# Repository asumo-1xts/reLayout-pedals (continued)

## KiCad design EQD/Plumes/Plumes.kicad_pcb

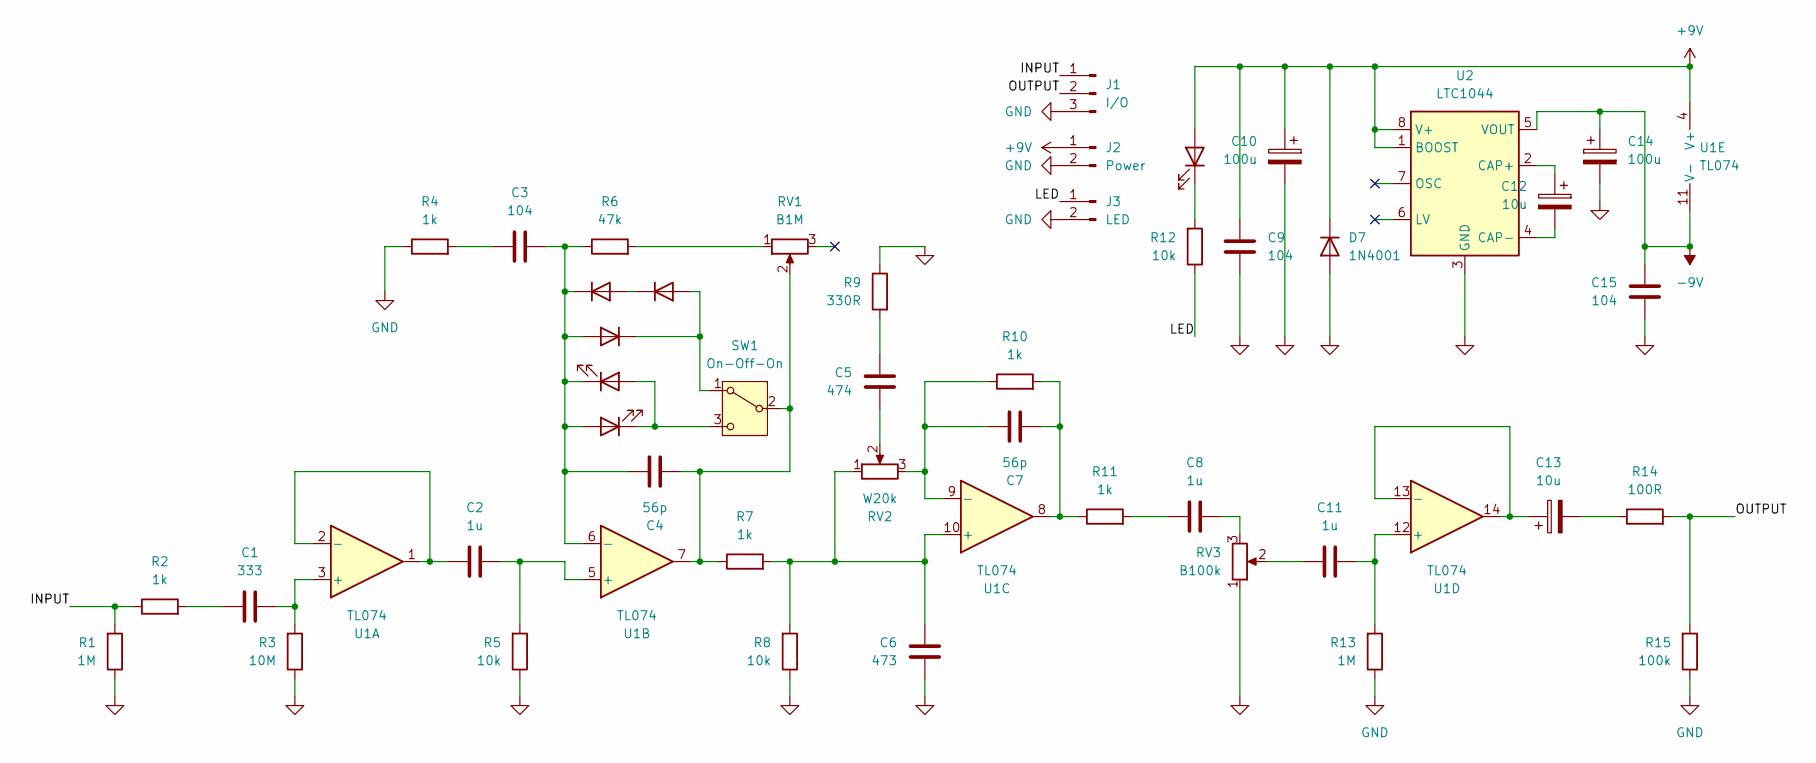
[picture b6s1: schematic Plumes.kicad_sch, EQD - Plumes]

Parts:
C1: 333; C_Rect_L7.2mm_W4.5mm_P5.00mm_FKS2_FKP2_MKS2_MKP2
C2, C8, C11: 1u; C_Rect_L7.0mm_W6.5mm_P5.00mm
C3: 104; C_Rect_L10.3mm_W5.7mm_P7.50mm_MKS4
C4, C7: 56p; C_Disc_D3.8mm_W2.6mm_P2.50mm
C5: 474; C_Rect_L7.2mm_W5.5mm_P5.00mm_FKS2_FKP2_MKS2_MKP2
C6: 473; C_Rect_L7.2mm_W4.5mm_P5.00mm_FKS2_FKP2_MKS2_MKP2
C9, C15: 104; C_Disc_D3.8mm_W2.6mm_P2.50mm
C10, C14: 100u; CP_Radial_D8.0mm_P3.50mm
C12, C13: 10u; CP_Radial_D5.0mm_P2.00mm
D1, D2, D5: 1N4148; D_DO-35_SOD27_P5.08mm_Vertical_AnodeUp
D3, D4, D6: LED; LED_D5.0mm
D7: 1N4001; D_DO-41_SOD81_P7.62mm_Horizontal
J1: I/O; PinHeader_1x03_P2.54mm_Vertical
J2: Power; PinHeader_1x02_P2.54mm_Vertical
J3: LED; PinHeader_1x02_P2.54mm_Vertical
R1, R13: 1M; R_Axial_DIN0207_L6.3mm_D2.5mm_P7.62mm_Horizontal
R2, R4, R7, R10, R11: 1k; R_Axial_DIN0207_L6.3mm_D2.5mm_P7.62mm_Horizontal
R3: 10M; R_Axial_DIN0207_L6.3mm_D2.5mm_P7.62mm_Horizontal
R5, R8, R12: 10k; R_Axial_DIN0207_L6.3mm_D2.5mm_P7.62mm_Horizontal
R6: 47k; R_Axial_DIN0207_L6.3mm_D2.5mm_P7.62mm_Horizontal
R9: 330R; R_Axial_DIN0207_L6.3mm_D2.5mm_P7.62mm_Horizontal
R14: 100R; R_Axial_DIN0207_L6.3mm_D2.5mm_P7.62mm_Horizontal
R15: 100k; R_Axial_DIN0207_L6.3mm_D2.5mm_P7.62mm_Horizontal
RV1: B1M; Potentiometer_Omeg_PC16BU_Vertical
RV2: W20k; Potentiometer_Omeg_PC16BU_Vertical
RV3: B100k; Potentiometer_Omeg_PC16BU_Vertical
SW1: On-Off-On; PinHeader_1x03_P2.54mm_Vertical
U1: TL074; DIP-14_W7.62mm
U2: LTC1044; DIP-8_W7.62mm

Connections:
+9V: C9.2, C10.1, D6.2 (A), D7.1 (K), J2.1, U1.4 (V+), U2.1 (BOOST), U2.8 (V+)
-9V: C14.1, C15.2, U1.11 (V-), U2.5 (VOUT)
/INPUT: J1.1, R1.2, R2.1
/LED: J3.1, R12.1
/OUTPUT: J1.2, R14.2, R15.2
GND: C6.1, C9.1, C10.2, C14.2, C15.1, D7.2 (A), J1.3, J2.2, J3.2, R1.1, R3.1, R4.1, R5.1, R8.1, R9.1, R13.1, R15.1, RV3.1, U2.3 (GND)
unnamed: C1.1, R2.2
unnamed: C3.1, R4.2
unnamed: C5.1, RV2.2
unnamed: C5.2, R9.2
unnamed: C7.2, R10.2, R11.1, U1.8
unnamed: C8.1, R11.2
unnamed: C8.2, RV3.3
unnamed: C11.1, RV3.2
unnamed: C13.2, R14.1
unnamed: D1.2 (A), D5.1 (K)
unnamed: C3.2, C4.1, D1.1 (K), D2.2 (A), D3.1 (K), D4.2 (A), R6.1, U1.6 (-)
unnamed: D2.1 (K), D5.2 (A), SW1.1 (A)
unnamed: D3.2 (A), D4.1 (K), SW1.3 (C)
unnamed: D6.1 (K), R12.2
unnamed: R6.2, RV1.1
unnamed: C4.2, R7.1, RV1.2, SW1.2 (B), U1.7
unnamed: C1.2, R3.2, U1.3 (+)
unnamed: C2.1, U1.1, U1.2 (-)
unnamed: C2.2, R5.2, U1.5 (+)
unnamed: C6.2, R7.2, R8.2, RV2.1, U1.10 (+)
unnamed: C7.1, R10.1, RV2.3, U1.9 (-)
unnamed: C11.2, R13.2, U1.12 (+)
unnamed: C13.1, U1.13 (-), U1.14
unnamed: C12.1, U2.2 (CAP+)
unnamed: C12.2, U2.4 (CAP-)

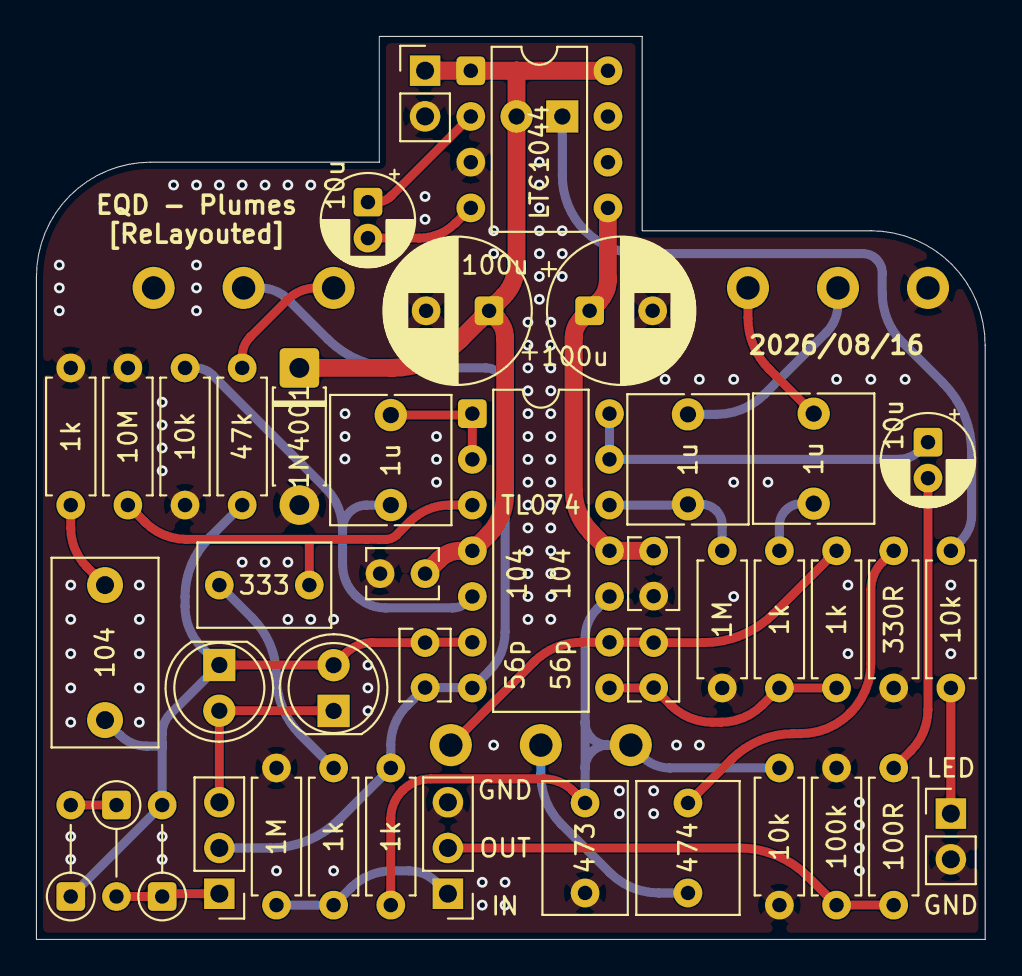
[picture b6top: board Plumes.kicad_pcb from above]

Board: 2 copper layers, 52.7 x 50.2 mm, 46 parts (1 on the bottom side), 31 nets.
